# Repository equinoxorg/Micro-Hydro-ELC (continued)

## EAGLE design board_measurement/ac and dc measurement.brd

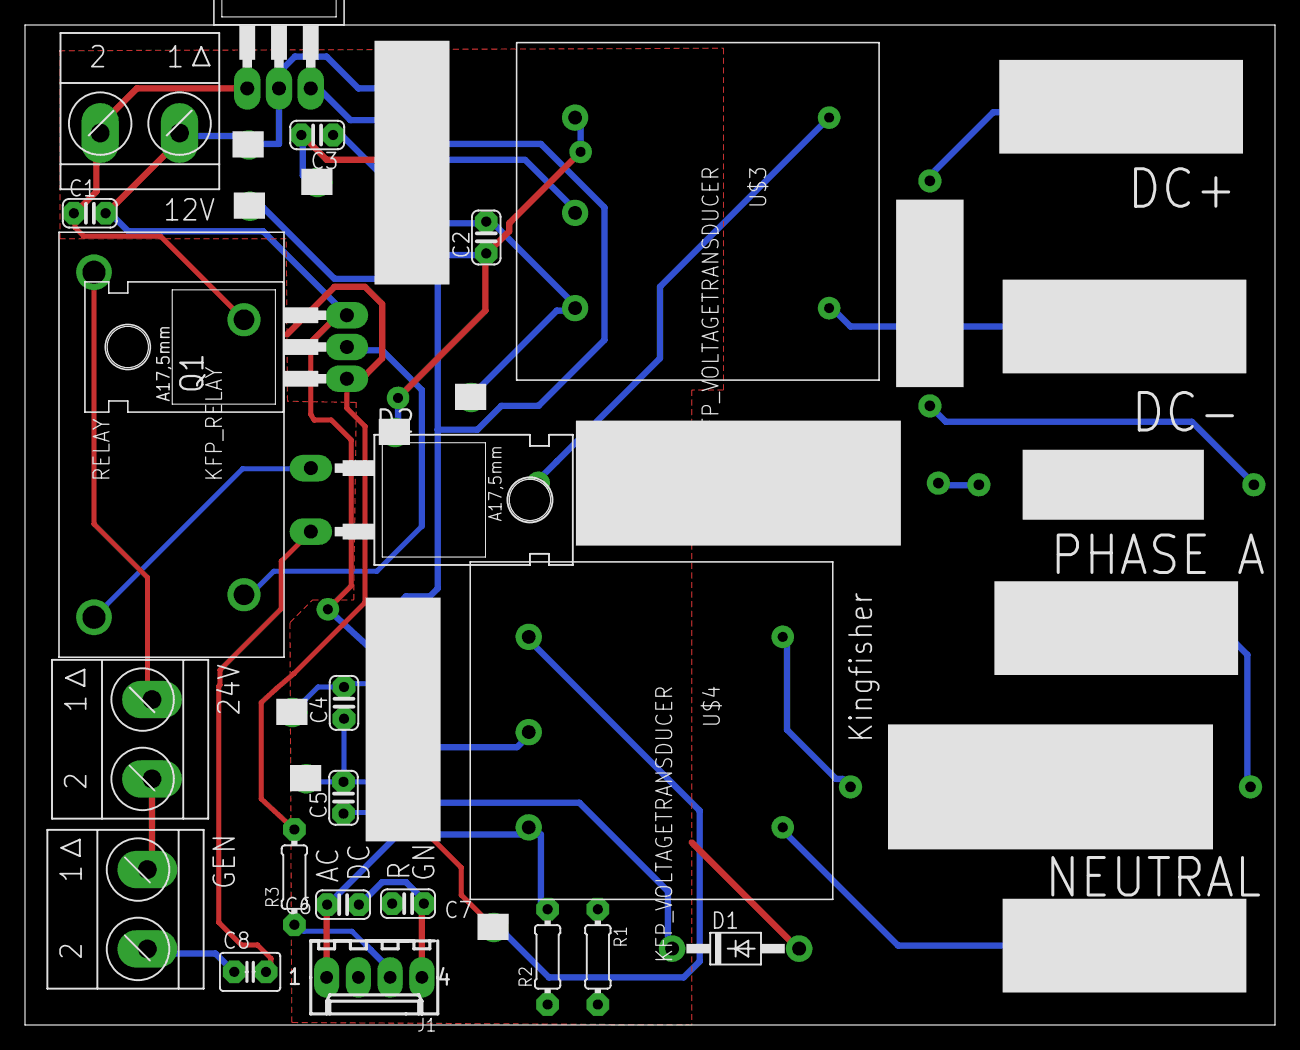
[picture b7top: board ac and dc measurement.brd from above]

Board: 2 copper layers, 100.0 x 80.0 mm, 40 parts (0 on the bottom side), 28 nets.

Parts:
5V: KFP_VOL_REG; TO220
12V, 24V: AKL701_215; AKL701_2_15
C1, C2, C3, C4, C5, C6, C7: C025-024X044
C8: C025-030X050
D1: 1N4004; DO41-10
D2: MBR750; TO220AC
GEN: AKL701_215; AKL701_2_15
J1: 22-27-2041-04; 6410-04
Q1: BUZ10; TO220
R1, R2, R3: 0204/7
RELAY: KFP_RELAY; KFP_RELAYSPST
U$1, U$2: KFP_DC_DC; KFP_DC-DC
U$3, U$4: KFP_VOLTAGETRANSDUCER
U$5, U$6: KFP_33K
U$7: KFP_22K
U$8: KFP_18K
U$9, U$11, U$12, U$13: HIGH_AMP_TERMINAL
U$14, U$15, U$16, U$17, U$18, U$19, U$20, U$21: KFP_TEST

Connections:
unnamed: 5V.2, 12V.1, C1.2, Q1.3, U$1.0V, U$2.0V, U$21.P$1
unnamed: 5V.3, U$1.+, U$2.+, U$16.P$1
unnamed: C3.2, U$3.+, U$14.P$1
unnamed: C4.2, U$2.-VOUT, U$4.+, U$18.P$1
unnamed: C6.2, C7.2, J1.4
unnamed: C2.1, U$1.+VOUT, U$3.-, U$15.P$1
unnamed: C4.1, C5.2, D1.C, U$2.0VOUT, U$20.P$1
unnamed: C5.1, U$2.+VOUT, U$4.-, U$17.P$1
unnamed: 24V.2, GEN.1
unnamed: U$4.+HT], U$5.P$1
unnamed: C6.1, J1.1, R2.2, U$4.M
unnamed: U$3.+HT], U$6.P$1
unnamed: U$6.P$2, U$7.P$1
unnamed: Q1.2, RELAY.A1
unnamed: U$5.P$2, U$12.P$1, U$12.P$2
unnamed: U$4.-HT, U$13.P$1, U$13.P$2
unnamed: Q1.1, R3.2
unnamed: U$3.-HT, U$11.P$1, U$11.P$2
unnamed: C8.1, GEN.2
unnamed: C8.2, D2.A
unnamed: U$8.P$2, U$9.P$1, U$9.P$2
unnamed: C2.2, C7.1, D1.A, J1.2, R1.1, R1.2, R2.1, U$1.0VOUT, U$3.M, U$19.P$1
unnamed: C3.1, U$1.-VOUT
unnamed: J1.3, R3.1
unnamed: 5V.1, 12V.2, C1.1, RELAY.A2
unnamed: D2.C, RELAY.11
unnamed: 24V.1, RELAY.14
RESISTOR: U$7.P$2, U$8.P$1

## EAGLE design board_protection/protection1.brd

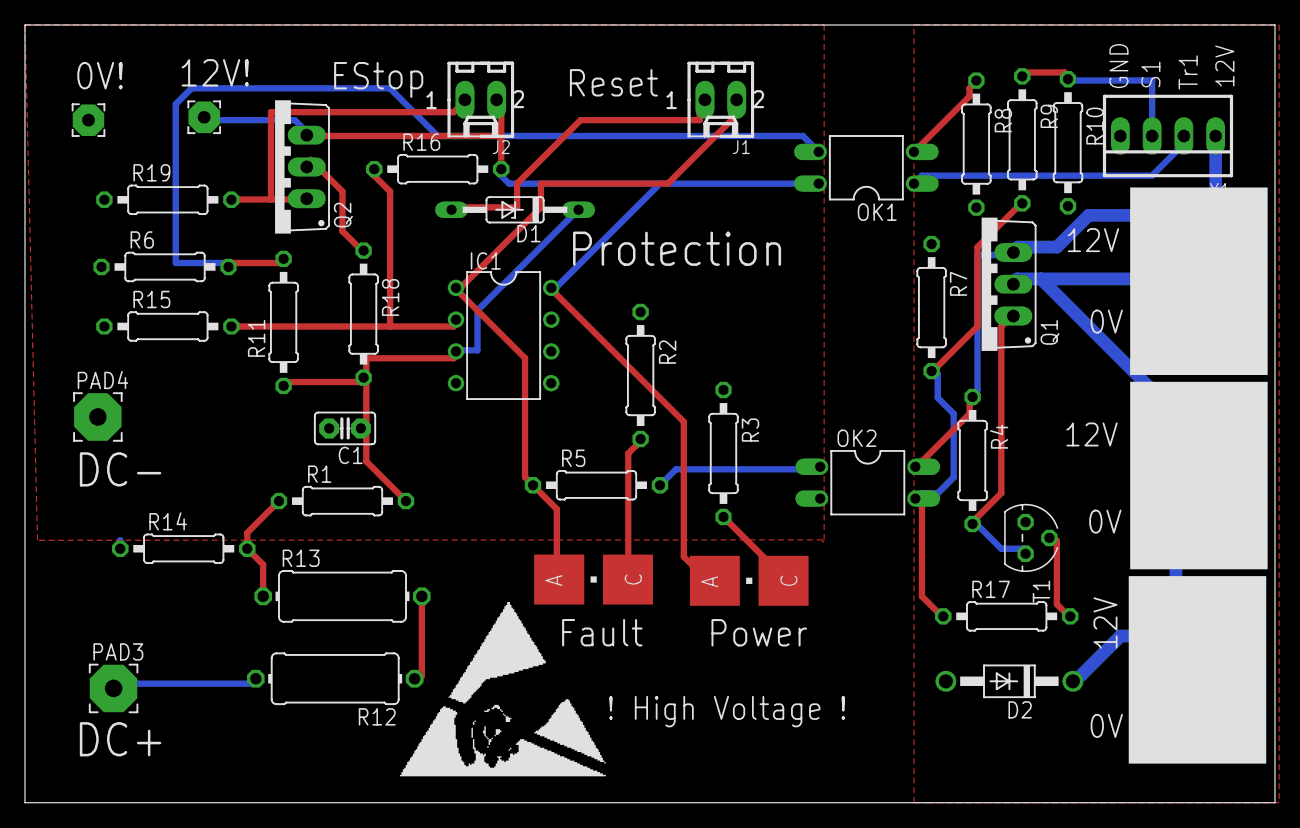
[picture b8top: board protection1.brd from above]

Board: 2 copper layers, 100.0 x 62.2 mm, 40 parts (0 on the bottom side), 24 nets.

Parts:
C1: C2.5-2
D1: 1N821; DO35Z10
D2: 1N4004; DO41-10
IC1: MC33078P; DIL08
J1, J2: 22-27-2021-02; 6410-02
LED1, LED2: P-LCC-2
OK1, OK2: TIL191; DIL04
PAD1, PAD2: 2,54/1,0
PAD3, PAD4: 3,81/1,4
Q1, Q2: IRF9530; TO220BV
R1, R2, R3, R4, R5, R6, R7, R8, R9, R10, R11, R14, R15, R16, R17, R18, R19: 0207/10
R12, R13: 0411/12
T1: 2N3904; TO92
U$1, U$2, U$3: TERMINAL_2WAY_EESTORES
X1: 22-23-2041

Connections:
12V: OK2.4, Q1.S, R4.1, X1.1
12V_A: IC1.8, J2.2, LED1.A, OK1.4, PAD1.1, Q2.S, R16.2
DC+: PAD3.1, R12.2
FAULT: IC1.1, J1.2, LED2.A, R5.1
FAULT_B: OK2.3, R7.2, R9.2, R17.1
F_TRIGGER: OK1.3, R6.2, R11.2
F_TRIGGER_B: OK1.1, X1.2
GND: D2.A, R7.1, R8.2, R10.2, T1.3, U$1.P$1, U$2.P$1, U$3.P$1, X1.4
GND_A: C1.2, IC1.4, OK2.2, PAD2.1, PAD4.1, R2.1, R3.1, R6.1, R14.1, R15.1, R19.1
unnamed: OK2.1, R5.2
unnamed: C1.1, D1.C, IC1.3, R1.2, R11.1, R18.2
unnamed: LED2.C, R2.2
unnamed: Q1.G, R4.2, T1.1
unnamed: IC1.2, R15.2, R16.1
unnamed: R17.2, T1.2
unnamed: R1.1, R13.1, R14.2
unnamed: LED1.C, R3.2
unnamed: R12.1, R13.2
unnamed: D2.C, Q1.D, U$1.P$2, U$2.P$2, U$3.P$2
unnamed: OK1.2, R8.1
unnamed: R9.1, R10.1, X1.3
unnamed: D1.A, J1.1
unnamed: Q2.D, R18.1
unnamed: J2.1, Q2.G, R19.2
